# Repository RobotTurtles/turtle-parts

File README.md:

turtle-parts
============

Physical Parts to Turtles

All CAD files are created using OpenSCAD, you can download openSCAD here: http://www.openscad.org/downloads.html

When creating new parts, please include both the scad file as well as a compiled STL for easy download.

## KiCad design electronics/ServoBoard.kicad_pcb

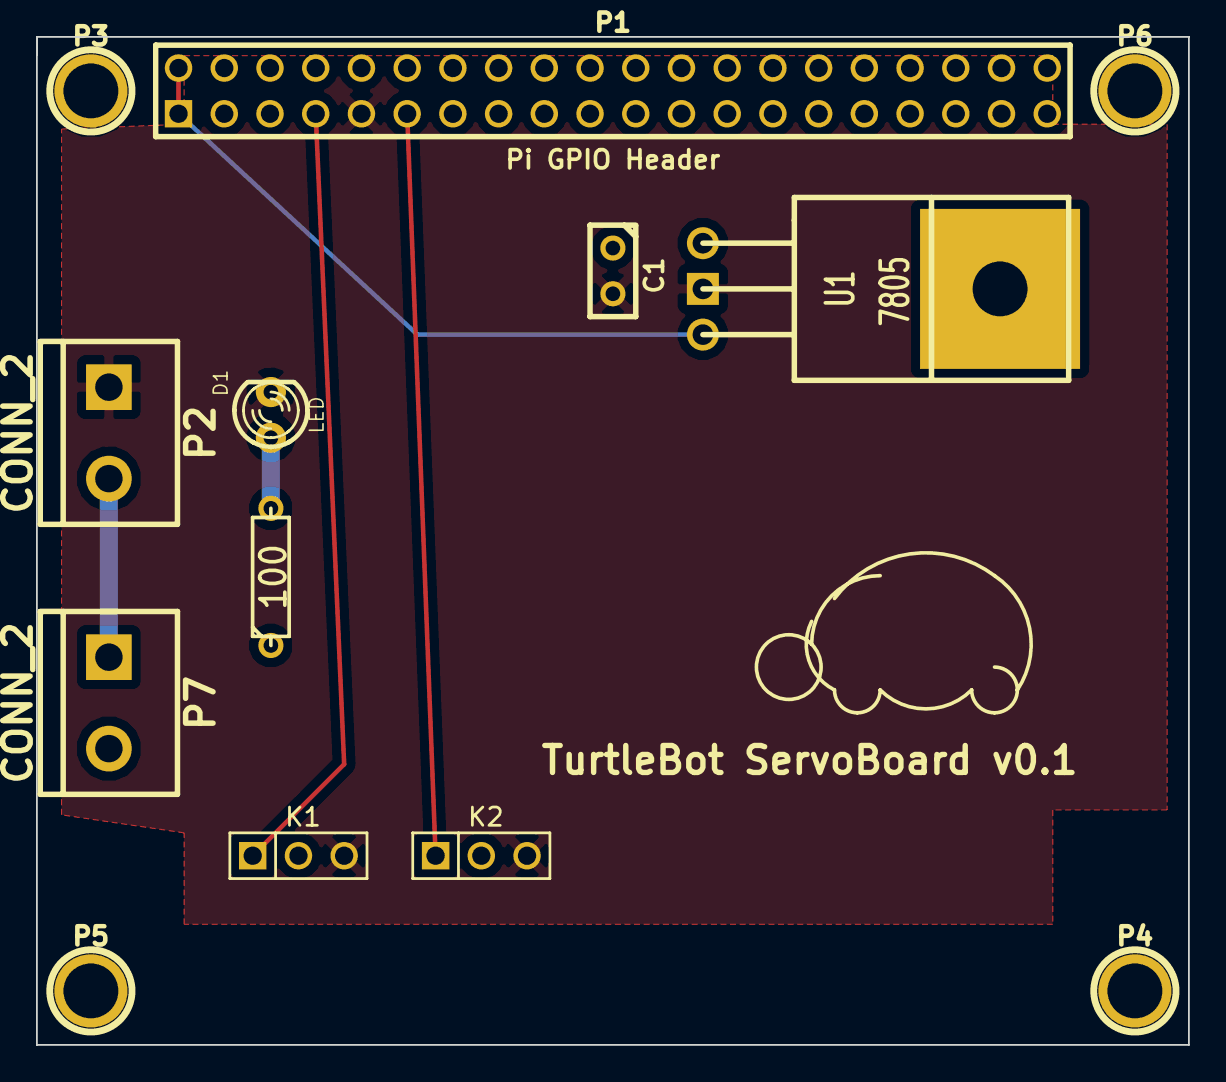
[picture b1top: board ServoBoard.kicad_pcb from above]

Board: 2 copper layers, 64.0 x 56.0 mm, 13 parts (0 on the bottom side), 7 nets.

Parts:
C1: 100 uF; C1
D1: LED; LED-3MM
K1: Left Servo; PIN_ARRAY_3X1
K2: Right Servo; PIN_ARRAY_3X1
P1: Pi GPIO Header; PIN_ARRAY_20X2
P2, P7: CONN_2; bornier2
P3, P4, P5, P6: CONNECTOR; 1pin
R1: 100; R3
U1: 7805; LM78XX

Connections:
+6V: C1.1, K1.2, K2.2, P7.2, R1.1, U1.VI
GND: C1.2, D1.2, K1.3, K2.3, P1.9, P2.1, U1.GND
unnamed: K1.1, P1.7
unnamed: K2.1, P1.11
unnamed: D1.1, R1.2
unnamed: P2.2, P7.1
unnamed: P1.1, P1.2, U1.VO

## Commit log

2014-11-01 Initial Commit of Robot Turtle Base
2014-11-01 Added a Battery Compartment (still rough, need to allow room for electrical wiring)
2014-11-02 Changed Battery Cover Cavity to not have dip
2014-11-02 Made Battery slightly taller, re-centered box
2014-11-05 Updated to flip base, and add caster
2014-11-06 Added Non Printed Parts List
2014-11-07 Added Battery Contacts to Battery Box
2014-11-07 Added STL File (forgot in last commit)
2014-11-07 Made Battery End Contacts "thicker" to allow insertion of digikey part
2014-11-07 Further Updating thickness
2014-11-08 Added an initial Turtle Shell
2014-11-08 Trying to work on cavity, having problems with Polyhedron
2014-11-09 Updated Robot Base to allow room for batteries. Had to modify cover and cavity to do so.
2014-11-09 Slowly trying to figure out why the cavity of the robot shell isn't working as expected.
2014-11-09 Got a cavity which compiles
2014-11-09 Successfully made cavity for robot shell. Still can be improved, but at least it compiles.
    As part of this, updated BasePlate to take a parameter.
2014-11-09 Trying to create bounding box for printrbot
2014-11-09 Working Printrbot cut
2014-11-10 Electronics! We'll probably have to adjust them slightly to fit them under the shell...
2014-11-11 Updated Robot Base to make battery contacts slightly tighter
2014-11-11 too small, increased contact thickness
2014-11-12 Robot Shell
2014-11-12 Updated Robot Base
2014-11-12 Added Screw Holes (first cut)
2014-11-12 Modified shell to enable Raspberry Pi to be mounted inside (worried about overhangs, but we'll see how it prints)
2014-11-14 Trying a different way to print
2014-11-14 rev2
2014-11-15 Updated Shell, made hole pattern its own module
2014-11-15 Updated Robot Base w/ New Battery Contacts, flipped cavity so terminals are closest to tail
2014-11-17 Updated to use Raspberry Pi
2014-11-17 Updated Build of Materials
2014-11-17 Added an inset for Holes, made dual contacts thicker and more space to place. Moved up servo cable hole.
2014-11-21 Updated to have a "curved" up to hole. This should allow it to print cleanly
2014-11-22 Slight update to the robot leg
2014-11-22 Made box cover slightly smaller than base
2014-11-24 Updated Legs to fit servo
2014-11-24 Updated Robot Legs, and Shell
2014-11-25 Updated Shell to be rounder, and have a cleaner cavity Removed holes front/aft Allowing webcam Usb plug to get through front opening
2014-11-26 Changed to a tent. Should print slightly better.
2014-11-28 Updated hole pattern, changing direction of insets. Made Base under shell "taller" to give room for electronics Updated Battery Contacts so it will fit better by default
2014-12-01 Updated Build of Materials to include a wifi adapter Updated Robot Leg to no longer be circular
2014-12-03 Trying to improve center of mass to be closer to over wheels. Shifted battery box as much as I can, flipped mount direction of servos (requiring a cut out for wires)
2014-12-03 Moved Files around to new directories
2014-12-06 Updated Robot Leg to have fine level of spikes
2014-12-07 Repaired (seems like there is a problem?)
2014-12-07 Updated to use sin/cos rather than calculate a circle... works much better...
2014-12-07 Added more room for servo cable
2014-12-07 Major update, added 5th battery
2014-12-07 Recompiled shell with new hole pattern
2014-12-08 Made base wider, battery thicker
2014-12-08 Increased width (which also makes it longer) Needed to give slightly more room for screw holes. Adjusted battery box (wasn't giving enough room for batteries) Updated Noch hole location (was incorrec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
2014-12-09 Fixed zip tie holes
2014-12-13 Reverted to 4 cells for batteries, thickened battery wall.
2014-12-13 Updated with 4 AA battery size
2014-12-19 Latest version with spot for switch on shell and spikeier legs
2015-01-02 Initial cut at a PCB for servos. Currently only a schematic
2015-01-02 Update to Battery Box Cover
2015-01-03 Gerber Files
2015-01-04 Updated to be 5.6 x 6.5cm in width/length.
    Moved pins to be over correct location.
2015-01-05 Added 2nd connector for power, may be a bit too small
2015-01-05 Created mount points for Raspberry Pi
2015-01-06 Updated to use screw terminals
2015-01-06 Updated Robot Base (including mount holes for Raspberry Pi)
2015-01-06 Increased mount hole diameter
2015-01-06 Updated issue with battery tabs not showing...
2015-02-25 Updated Parts List
2015-03-17 Updated BOM with latest pricing info,
2015-03-18 Latest Working code. Green Shell, Orange and Purple bases. Note: 70% fill for base.
2015-12-18 Slightly modified battery height. Updated Bill of Materials to reflect current single unit pricing
2015-12-18 Updated Build of Materials to include taxes
2015-12-21 Increased Diameters for screws, and made them more round. Increased battery cover hole to be slightly larger in x Increased "width" for servo body
2015-12-21 Minor tweaks to get rid of "overhangs" into battery compartment
2015-12-21 Cover isn't quite wide enough
2015-12-22 Updated Build of Materials to include battery cost
2015-12-22 Updated Print Cover to have slightly shorter tabs
2017-07-15 Added a first cut of a shell with bumps
